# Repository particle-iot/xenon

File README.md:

# Xenon

<div align=center></div>

### Overview

The Xenon is a low cost mesh-enabled development board that can act as either an endpoint or repeater within a Particle Mesh network.

The Xenon is mesh only and designed to function as the endpoint of your IoT network. It is based on the Nordic nRF52840 and has built-in battery charging circuitry so it’s easy to connect a Li-Po and deploy your local network in minutes.

The Xenon is best for connecting sensors, motors, pumps, valves, and points of data-interest. Pair it with an Argon or Boron gateway to get all that great data into the Device Cloud.

### Features

* Nordic Semiconductor nRF52840 SoC 
  * ARM Cortex-M4F 32-bit processor @ 64MHz 
  * 1MB flash, 256KB RAM 
  * IEEE 802.15.4-2006: 250 Kbps 
  * Bluetooth 5: 2 Mbps, 1 Mbps, 500 Kbps, 125 Kbps 
  * Supports DSP instructions, HW accelerated Floating Point Unit (FPU) calculations 
  * ARM TrustZone CryptoCell-310 Cryptographic and security module 
  * Up to +8 dBm TX power (down to -20 dBm in 4 dB steps) 
  * NFC-A tag
* On-board additional 2MB SPI flash
* 20 mixed signal GPIO (6 x Analog, 8 x PWM), UART, I2C, SPI
* Micro USB 2.0 full speed (12 Mbps)
* Integrated Li-Po charging and battery connector
* JTAG (SWD) Connector
* RGB status LED
* Reset and Mode buttons
* On-board PCB antenna
* u.FL connector for external antenna
* Meets the Adafruit Feather [specification](https://learn.adafruit.com/adafruit-feather/feather-specification) in dimensions and pinout
* FCC, CE and IC certified
* RoHS compliant (lead-free)

### Structure of this repository:
 - /eagle
     + Contains the schematic and PCB files in the Eagle file format
 - /gerbers
     + Contains the manufacturing gerber files for the board
 - /datasheets
     + Contains the relevant datasheets of the components used on the Xenon
 - /pdfs
     + Contains schematic files in PDF 

### Hardware datasheet

The complete datasheet for the Xenon is available [here.](https://docs.particle.io/datasheets/mesh/xenon-datasheet/)

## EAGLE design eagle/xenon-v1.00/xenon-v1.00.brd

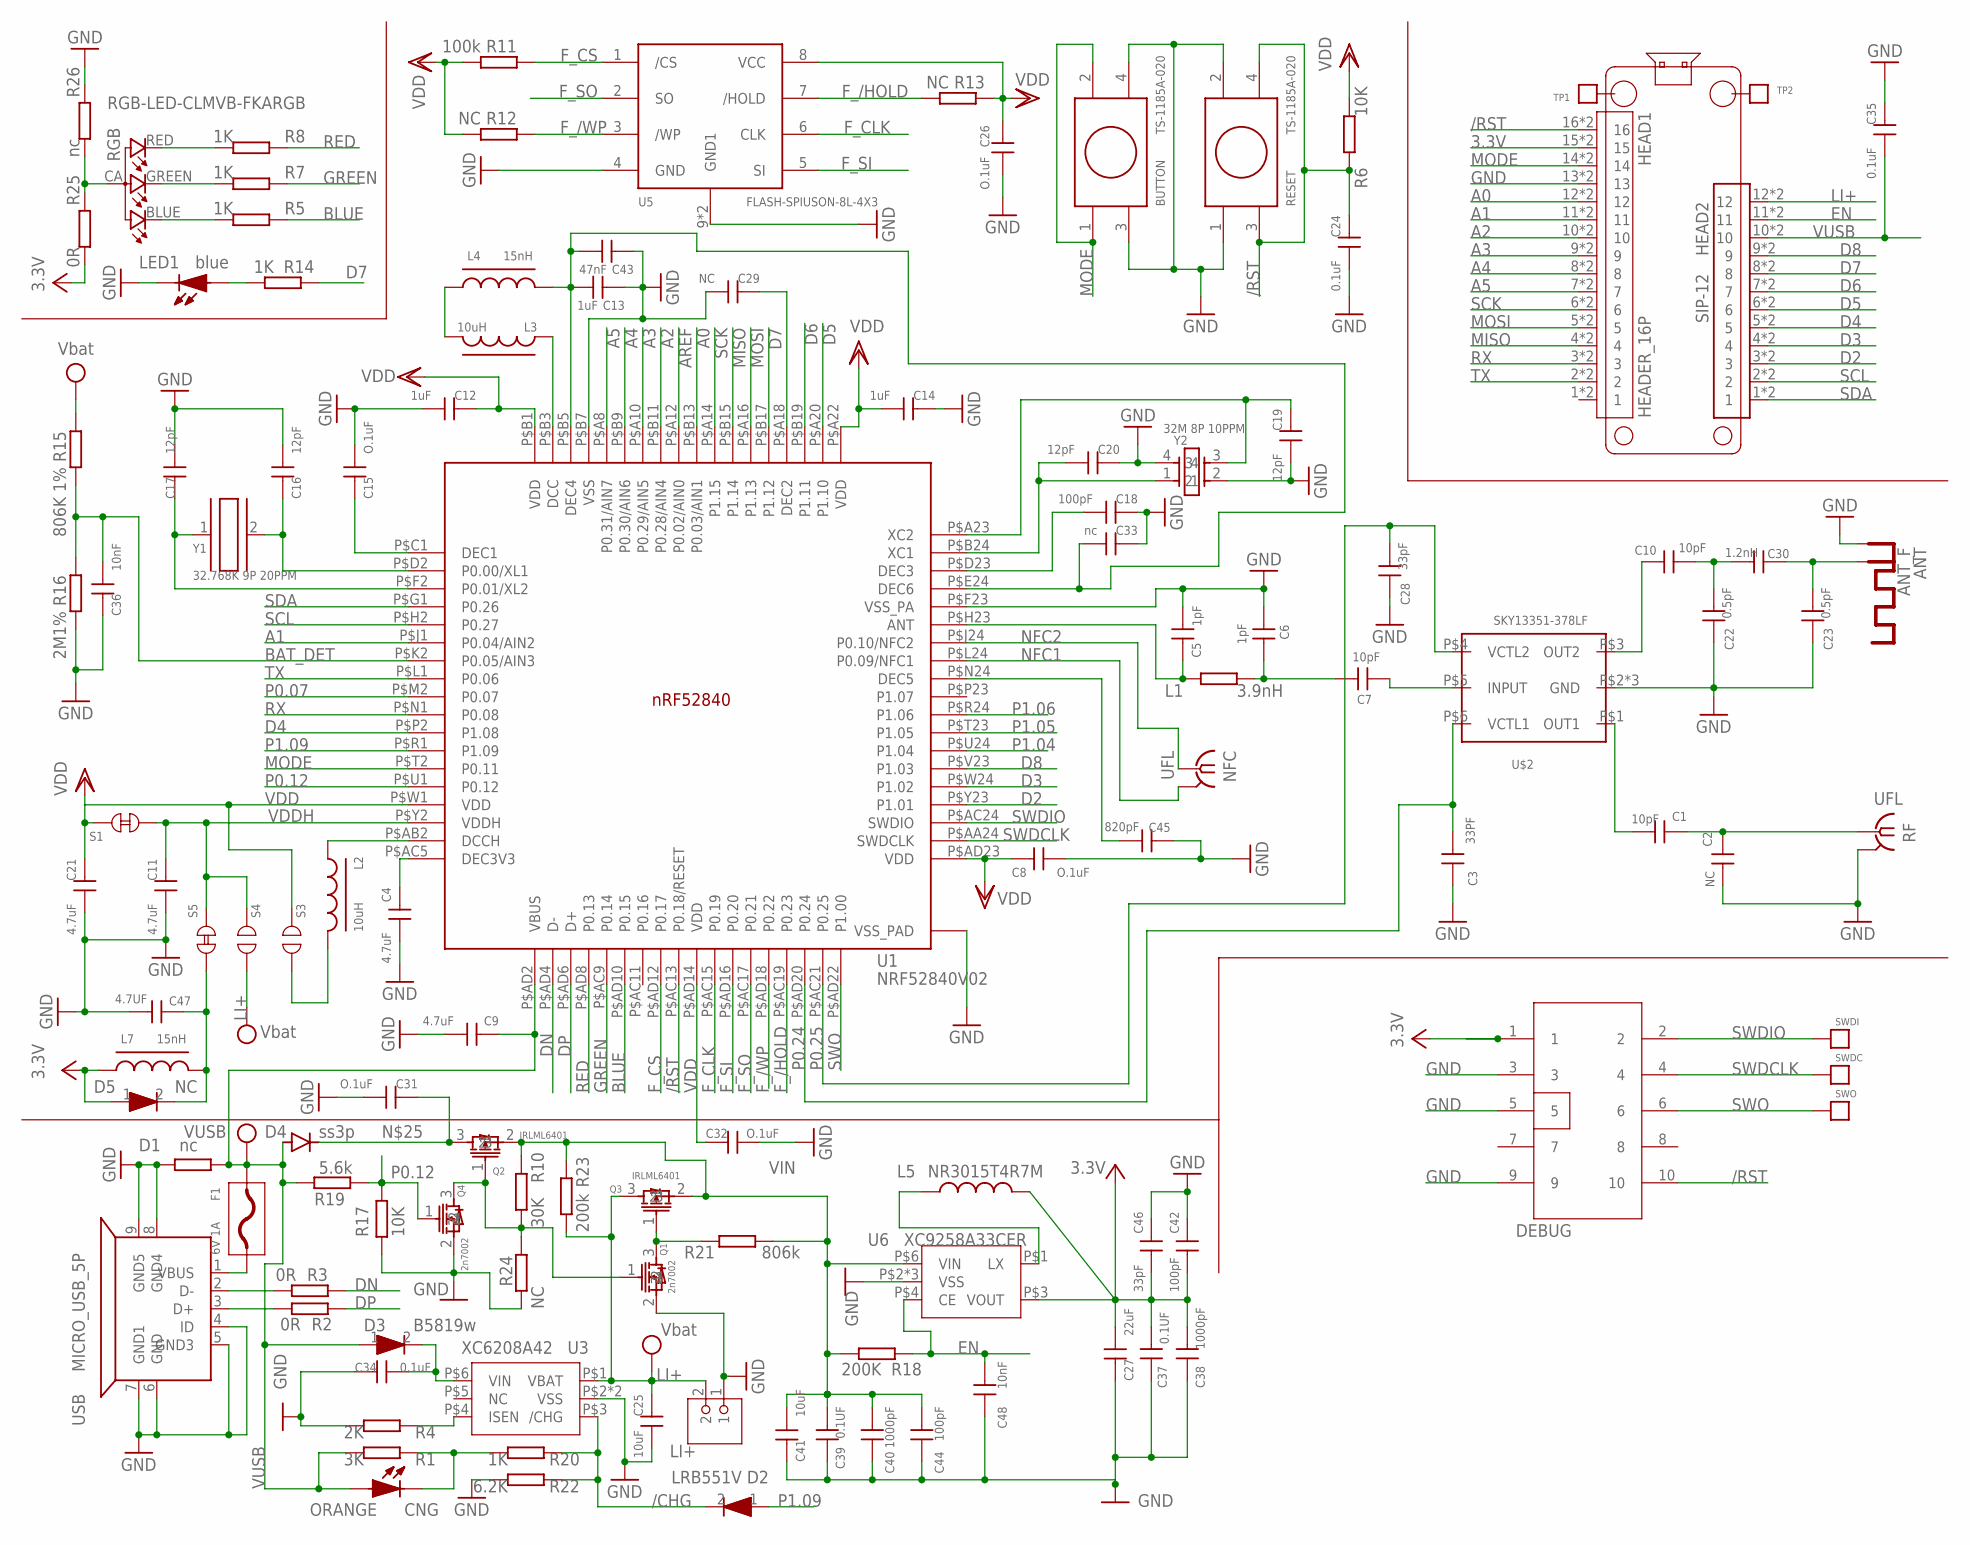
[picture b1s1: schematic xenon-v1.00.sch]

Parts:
ANT: ANT_F; ANTENNA_F2_PCB
BAT: CON2P_SMT; CON_2.0MM_SMT
BUTTON: TS-1185A-020
C1, C7, C10: 10pF; C-0402
C2, C29: NC; C-0402
C3: 33PF; C-0402
C4, C9, C11, C21: 4.7uF; C-0402
C5, C6: 1pF; C-0402
C8, C15, C26, C31, C32: O.1uF; C-0402
C12, C13, C14: 1uF; C-0402
C16, C17, C19, C20: 12pF; C-0402
C18, C42, C44: 100pF; C-0402
C22, C23: 0.5pF; C-0402
C24, C34, C35: 0.1uF; C-0402
C25: 10uF; C0805
C27: 22uF; C0805
C28, C46: 33pF; C-0402
C30: 1.2nH; C-0402
C33: nc; C-0402
C36, C48: 10nF; C-0402
C37, C39: 0.1UF; C-0402
C38, C40: 1000pF; C-0402
C41: 10uF; C0603
C43: 47nF; C-0402
C45: 820pF; C-0402
C47: 4.7UF; C-0402
CNG: ORANGE; LED0603
D1: nc; R-0402S
D2: LRB551V; SOD-323
D3: B5819w; SOD-123
D4: ss3p; DIODE-DO-220AA(SMP)
D5: NC; SOD-323
DEBUG: CON5X2; CON5X2_1.27
F1: 6V 1A; F0805
HEAD1: HEADER_16P; HEADER_16P2.54
HEAD2: SIP-12
L1: 3.9nH; R-0402S
L2, L3: 10uH; R-0603A
L4, L7: 15nH; R-0402S
L5: NR3015T4R7M; INDUCTOR-NR3015
LED1: blue; LED0603
NFC: UFL; IPEX-20279-001E
Q1, Q4: 2n7002; SOT323
Q2, Q3: IRLML6401; SOT-23
R1: 3K; R-0402S
R2, R3, R25: 0R; R-0402S
R4: 2K; R-0402S
R5, R7, R8, R14, R20: 1K; R-0402S
R6, R17: 10K; R-0402S
R10: 30K; R-0402S
R11: 100k; R-0402S
R12, R13, R24: NC; R-0402S
R15: 806K 1%; R-0402S
R16: 2M1%; R-0402S
R18: 200K; R-0402S
R19: 5.6k; R-0402S
R21: 806k; R-0402S
R22: 6.2K; R-0402S
R23: 200k; R-0402S
R26: nc; R-0402S
RESET: TS-1185A-020
RF: UFL; IPEX-20279-001E
RGB: RGB-LED-CLMVB-FKARGB; PLCC4-2MM-RGB
S1, S5: TP_SHORT
S3, S4: TP_OPEN
SWDC: TPTP; TP
SWDI: TPTP; TP
SWO: TPTP; TP
TP1, TP2: TPTP2.5; TP-2.5
U1: NRF52840V02; AQN507X7X0.85_HA-74_V2
U3: XC6208A42; USP-6C
U5: FLASH-SPIUSON-8L-4X3; USON8-3X4
U6: XC9258A33CER; USP-6C
U$2: SKY13351-378LF; MLPD-6-1X1
USB: MICRO_USB_5P; MICRO_USB
Y1: 32.768K 9P 20PPM; CRY_3215
Y2: 32M 8P 10PPM; CRY_2520

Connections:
3.3V: C27.1, C37.2, C38.2, C42.2, C46.2, D5.1, DEBUG.1, HEAD1.15, HEAD1.P$15 (15), L5.2, L7.1, R25.2, U6.P$3 (VOUT)
/CHG: D2.2, R20.1, R22.1, U3.P$3 (/CHG)
/RST: C24.2, DEBUG.10, HEAD1.16, HEAD1.P$16 (16), R6.1, RESET.3, RESET.4, U1.P$AC13 (P0.18/RESET)
A0: HEAD1.12, HEAD1.P$12 (12), U1.P$B13 (P0.03/AIN1)
A1: HEAD1.11, HEAD1.P$11 (11), U1.P$J1 (P0.04/AIN2)
A2: HEAD1.10, HEAD1.P$10 (10), U1.P$B11 (P0.28/AIN4)
A3: HEAD1.9, HEAD1.P$9 (9), U1.P$A10 (P0.29/AIN5)
A4: HEAD1.8, HEAD1.P$8 (8), U1.P$B9 (P0.30/AIN6)
A5: HEAD1.7, HEAD1.P$7 (7), U1.P$A8 (P0.31/AIN7)
AREF: U1.P$A12 (P0.02/AIN0)
BAT_DET: C36.1, R15.2, R16.1, U1.P$K2 (P0.05/AIN3)
BLUE: R5.1, U1.P$AD10 (P0.15)
D2: HEAD2.3, HEAD2.P$3 (3), U1.P$Y23 (P1.01)
D3: HEAD2.4, HEAD2.P$4 (4), U1.P$W24 (P1.02)
D4: HEAD2.5, HEAD2.P$5 (5), U1.P$P2 (P1.08)
D5: HEAD2.6, HEAD2.P$6 (6), U1.P$A20 (P1.10)
D6: HEAD2.7, HEAD2.P$7 (7), U1.P$B19 (P1.11)
D7: HEAD2.8, HEAD2.P$8 (8), R14.1, U1.P$B17 (P1.12)
D8: HEAD2.9, HEAD2.P$9 (9), U1.P$V23 (P1.03)
D+: R2.2, USB.3 (D+)
D-: R3.2, USB.2 (D-)
DN: R3.1, U1.P$AD4 (D-)
DP: R2.1, U1.P$AD6 (D+)
EN: C48.2, HEAD2.11, HEAD2.P$11 (11), R18.1, U6.P$4 (CE)
F_/HOLD: R13.2, U1.P$AC19 (P0.23), U5.7 (/HOLD)
F_/WP: R12.1, U1.P$AD18 (P0.22), U5.3 (/WP)
F_CLK: U1.P$AC15 (P0.19), U5.6 (CLK)
F_CS: R11.1, U1.P$AD12 (P0.17), U5.1 (/CS)
F_SI: U1.P$AD16 (P0.20), U5.5 (SI)
F_SO: U1.P$AC17 (P0.21), U5.2 (SO)
GND: ANT.GND, BAT.1, BUTTON.3, BUTTON.4, C2.2, C3.1, C4.1, C5.1, C6.1, C8.1, C9.1, C11.1, C12.1, C13.2, C14.2, C15.1, C16.1, C17.1, C18.2, C19.1, C20.2, C21.1, C22.1, C23.1, C24.1, C25.1, C26.1, C27.2, C28.1, C29.1, C31.1, C32.1, C33.2, C34.2, C35.2, C36.2, C37.1, C38.1, C39.1, C40.1, C41.2, C42.1, C43.2, C44.1, C45.2, C46.1, C47.2, C48.1, D1.1, DEBUG.3, DEBUG.5, DEBUG.9, HEAD1.13, HEAD1.P$13 (13), LED1.2 (K), Q1.2, Q4.2, R4.2, R16.2, R17.1, R22.2, R24.1, R26.1, RESET.1, RESET.2, RF.2@1 (GND), RF.2@2 (GND), U1.P$74 (VSS_PAD), U1.P$75 (VSS_PAD), U1.P$76 (VSS_PAD), U1.P$77 (VSS_PAD), U1.P$78 (VSS_PAD), U1.P$79 (VSS_PAD), U1.P$80 (VSS_PAD), U1.P$81 (VSS_PAD), U1.P$82 (VSS_PAD), U1.P$85 (VSS_PAD), U1.P$B7 (VSS), U1.P$F23 (VSS_PA), U3.P$2 (VSS), U3.P$7 (VSS), U5.4 (GND), U5.9 (GND1), U5.10 (GND1), U6.P$2 (VSS), U6.P$5 (VSS), U6.P$7 (VSS), U$2.P$2 (GND), U$2.P$7 (GND), U$2.P$8 (GND), USB.4 (ID), USB.5 (GND3), USB.6 (GND), USB.7 (GND1), USB.8 (GND4), USB.9 (GND5), Y2.2, Y2.4
GREEN: R7.1, U1.P$AC9 (P0.14)
LI+: BAT.2, C25.2, HEAD2.12, HEAD2.P$12 (12), Q3.3, R15.1, R23.1, S4.1, U3.P$1 (VBAT)
MISO: HEAD1.4, HEAD1.P$4 (4), U1.P$B15 (P1.14)
MODE: BUTTON.1, BUTTON.2, HEAD1.14, HEAD1.P$14 (14), U1.P$T2 (P0.11)
MOSI: HEAD1.5, HEAD1.P$5 (5), U1.P$A16 (P1.13)
unnamed: L2.1, U1.P$AB2 (DCCH)
unnamed: C5.2, L1.1, U1.P$H23 (ANT)
unnamed: C6.2, C7.2, L1.2
unnamed: C16.2, U1.P$D2 (P0.00/XL1), Y1.2
unnamed: C13.1, C33.1, C43.1, L4.2, U1.P$B5 (DEC4), U1.P$E24 (DEC6)
unnamed: L3.2, L4.1
unnamed: L3.1, U1.P$B3 (DCC)
unnamed: C15.2, U1.P$C1 (DEC1)
unnamed: C17.2, U1.P$F2 (P0.01/XL2), Y1.1
unnamed: C1.1, C2.1, RF.1
unnamed: C19.2, U1.P$A23 (XC2), Y2.3
unnamed: C18.1, U1.P$D23 (DEC3)
unnamed: LED1.1 (A), R14.2
unnamed: L2.2, S3.1
unnamed: C20.1, U1.P$B24 (XC1), Y2.1
unnamed: C7.1, U$2.P$5 (INPUT)
unnamed: C10.1, U$2.P$3 (OUT2)
unnamed: F1.P$1 (1), USB.1 (VBUS)
unnamed: C47.1, D5.2, L7.2, S5.2
unnamed: CNG.2 (K), R1.1, R20.2
unnamed: R4.1, U3.P$4 (ISEN)
unnamed: R8.2, RGB.RED (4)
unnamed: R25.1, R26.2, RGB.CA (1)
unnamed: C31.2, D4.CATHODE, Q2.3
unnamed: R5.2, RGB.BLUE (2)
unnamed: R7.2, RGB.GREEN (3)
unnamed: C29.2, U1.P$A18 (DEC2)
unnamed: C4.2, U1.P$AC5 (DEC3V3)
unnamed: C45.1, U1.P$N24 (DEC5)
unnamed: C10.2, C22.2, C30.2
unnamed: ANT.RF, C23.2, C30.1
unnamed: Q1.1, Q2.1, Q4.3, R10.1, R24.2
unnamed: C1.2, U$2.P$1 (OUT1)
unnamed: C34.1, D3.2, U3.P$6 (VIN)
unnamed: Q1.3, Q3.1, R21.2
unnamed: L5.1, U6.P$1 (LX)
NFC1: NFC.2@1 (GND), NFC.2@2 (GND), U1.P$L24 (P0.09/NFC1)
NFC2: NFC.1, U1.P$J24 (P0.10/NFC2)
P0.07: U1.P$M2 (P0.07)
P0.12: Q4.1, R17.2, R19.2, U1.P$U1 (P0.12)
P0.24: C3.2, U1.P$AD20 (P0.24), U$2.P$6 (VCTL1)
P0.25: C28.2, U1.P$AC21 (P0.25), U$2.P$4 (VCTL2)
P1.04: U1.P$U24 (P1.04)
P1.05: U1.P$T23 (P1.05)
P1.06: U1.P$R24 (P1.06)
P1.09: D2.1, U1.P$R1 (P1.09)
RED: R8.1, U1.P$AD8 (P0.13)
RX: HEAD1.3, HEAD1.P$3 (3), U1.P$N1 (P0.08)
SCK: HEAD1.6, HEAD1.P$6 (6), U1.P$A14 (P1.15)
SCL: HEAD2.2, HEAD2.P$2 (2), U1.P$H2 (P0.27)
SDA: HEAD2.1, HEAD2.P$1 (1), U1.P$G1 (P0.26)
SWDCLK: DEBUG.4, SWDC.P$1, U1.P$AA24 (SWDCLK)
SWDIO: DEBUG.2, SWDI.P$1, U1.P$AC24 (SWDIO)
SWO: DEBUG.6, SWO.P$1, U1.P$AD22 (P1.00)
TX: HEAD1.2, HEAD1.P$2 (2), U1.P$L1 (P0.06)
VDD: C8.2, C12.2, C14.1, C21.2, C26.2, C32.2, R6.2, R11.2, R12.2, R13.1, S1.1, S3.2, U1.P$A22 (VDD), U1.P$AD14 (VDD), U1.P$AD23 (VDD), U1.P$B1 (VDD), U1.P$W1 (VDD), U5.8 (VCC)
VDDH: C11.2, S1.2, S4.2, S5.1, U1.P$Y2 (VDDH)
VIN: C39.2, C40.2, C41.1, C44.2, Q2.2, Q3.2, R10.2, R18.2, R21.1, R23.2, U6.P$6 (VIN)
VUSB: C9.2, C35.1, CNG.1 (A), D1.2, D3.1, D4.ANODE, F1.P$2 (2), HEAD2.10, HEAD2.P$10 (10), R1.2, R19.1, U1.P$AD2 (VBUS)

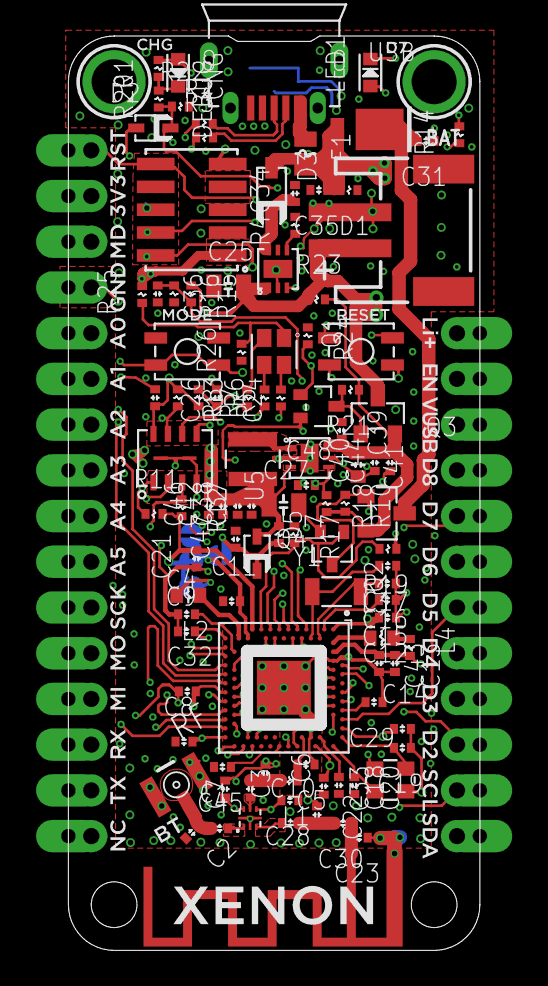
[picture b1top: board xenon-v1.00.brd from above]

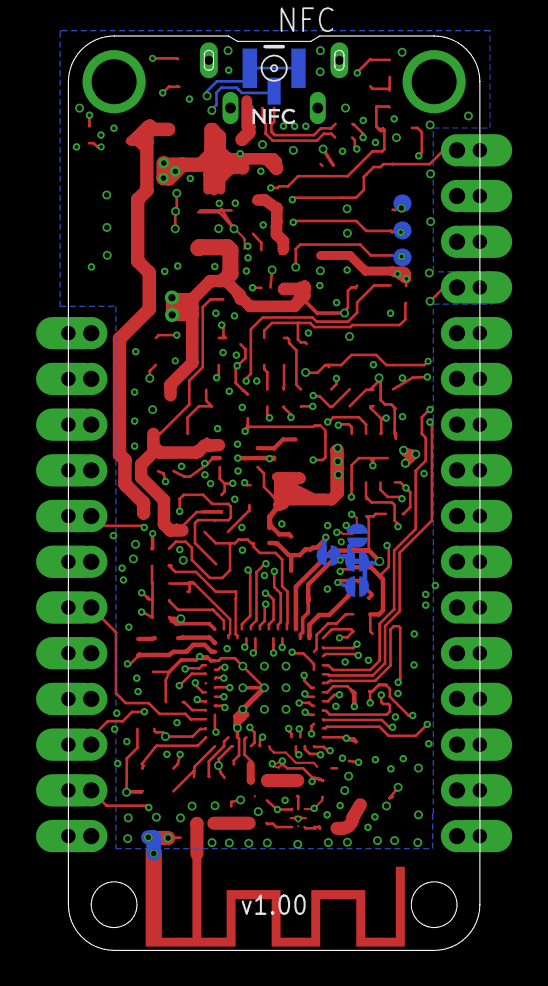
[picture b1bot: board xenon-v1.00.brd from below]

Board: 4 copper layers, 22.9 x 50.8 mm, 118 parts (8 on the bottom side), 90 nets.

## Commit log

2018-10-03 added design files
2018-10-30 updated readme and added datasheets
2018-10-30 fixed image link
2018-10-30 updated image size
2018-10-30 Fix bullets. Silly GFM.
2019-03-04 Include MX25L3233F SPI flash datasheet
